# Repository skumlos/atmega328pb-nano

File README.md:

Arduino Mini Pro clone with Atmega328PB

This is basically an Arduino Mini Pro clone but with an Atmega328PB instead of Atmega328P.

Speed 16MHz and 5V.

The reasoning is to have the secondary I2C controller of the PB version, thus PE0 and PE1
pins are pulled to 2.54mm THT holes just like A4/A5 pins of the primary I2C controller.

Remember to burn a bootloader and fuses with a *real* programmer (like another Arduino
turned into an ISP). This requires you to connect to the ICSP pins, MOSI, MISO, SCK,
RESET, 5V and GND. I used a male pin header row  which I didn't solder but just held in
place during programming.

The design is tested and works, but it is hacked together pretty quick so bugs are possible.

(2023) Martin Hejnfelt, martin@hejnfelt.com

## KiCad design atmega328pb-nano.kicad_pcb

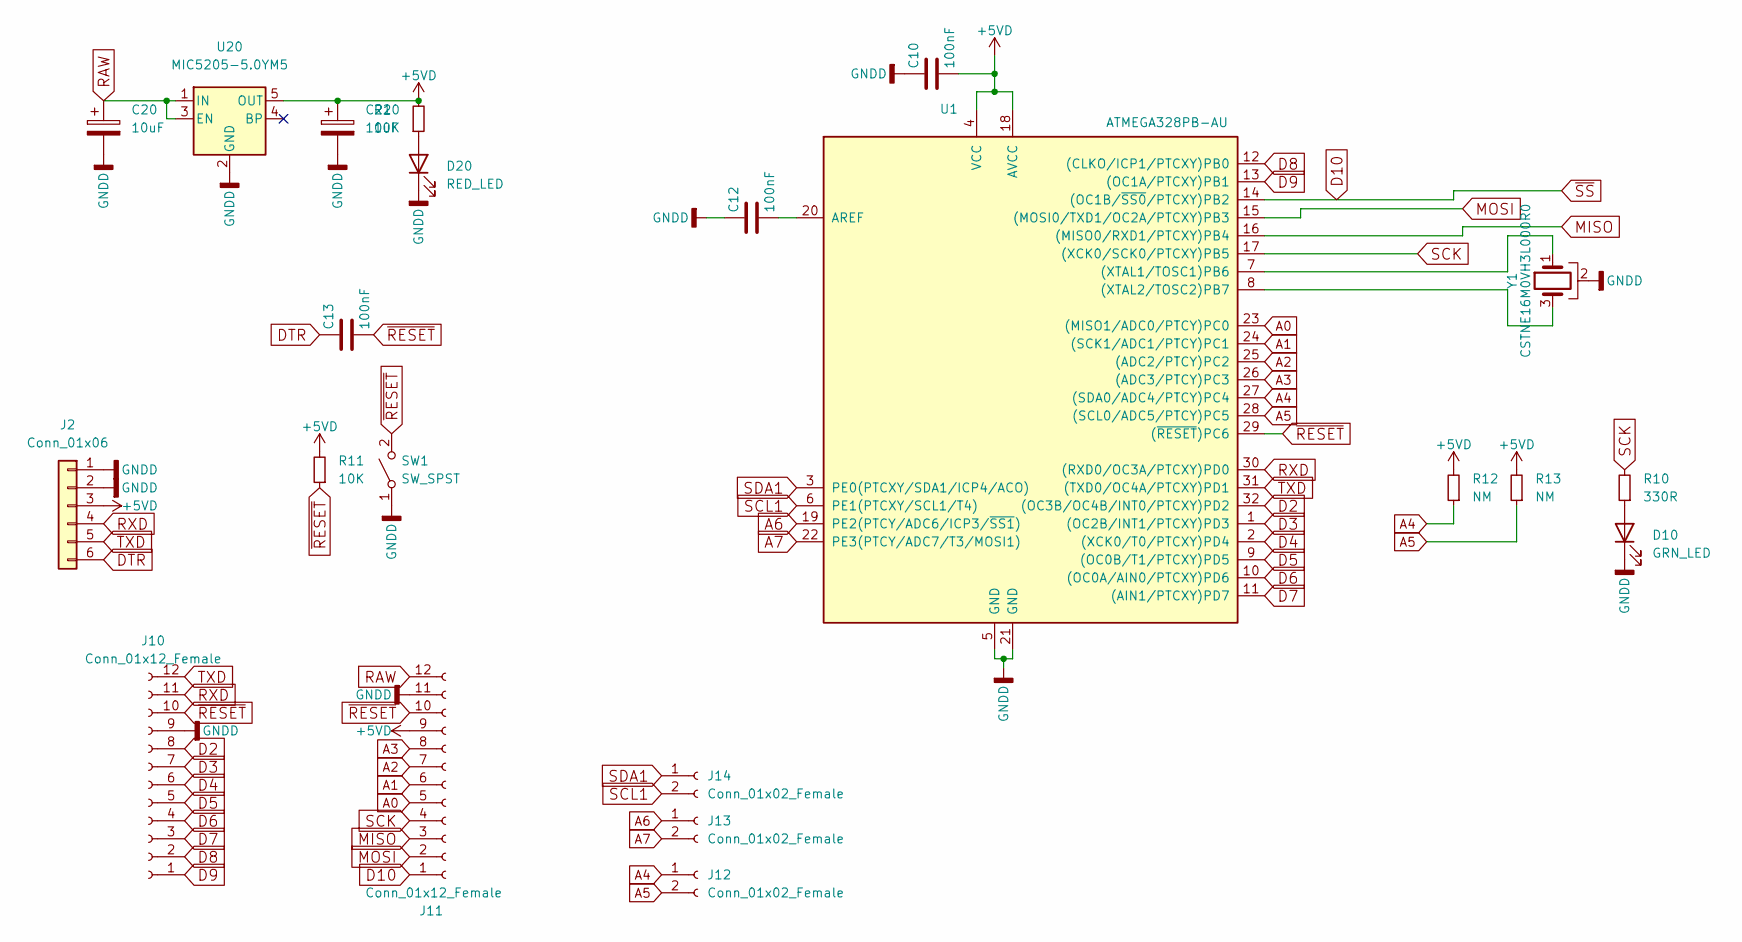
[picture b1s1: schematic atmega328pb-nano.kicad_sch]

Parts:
C10, C12, C13: 100nF; C_0603_1608Metric
C20, C21: 10uF; CP_EIA-3216-18_Kemet-A
D10: GRN_LED; LED_0603_1608Metric
D20: RED_LED; LED_0603_1608Metric
J2: Conn_01x06; PinHeader_1x06_P2.54mm_Horizontal
J10, J11: Conn_01x12_Female; PinHeader_1x12_P2.54mm_Vertical
J12, J13, J14: Conn_01x02_Female; PinHeader_1x02_P2.54mm_Vertical
R10: 330R; R_0603_1608Metric
R11, R20: 10K; R_0603_1608Metric
R12, R13: NM; R_0603_1608Metric
SW1: SW_SPST; SW_Tactile_SPST_NO_Straight_CK_PTS636Sx25SMTRLFS
U1: ATMEGA328PB-AU; TQFP-32_7x7mm_P0.8mm
U20: MIC5205-5.0YM5; SOT-23-5
Y1: CSTNE16M0VH3L000R0; Resonator_SMD_Murata_CSTxExxV-3Pin_3.0x1.1mm

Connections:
+5VD: C10.2, C21.1, J2.3, J11.9, R11.2, R12.2, R13.2, R20.2, U1.4 (VCC), U1.18 (AVCC), U20.5 (OUT)
A0: J11.5, U1.23 ((MISO1/ADC0/PTCY)PC0)
A1: J11.6, U1.24 ((SCK1/ADC1/PTCY)PC1)
A2: J11.7, U1.25 ((ADC2/PTCY)PC2)
A3: J11.8, U1.26 ((ADC3/PTCY)PC3)
A4: J12.1, R12.1, U1.27 ((SDA0/ADC4/PTCY)PC4)
A5: J12.2, R13.1, U1.28 ((SCL0/ADC5/PTCY)PC5)
A6: J13.1, U1.19 (PE2(PTCY/ADC6/ICP3/~SS1))
A7: J13.2, U1.22 (PE3(PTCY/ADC7/T3/MOSI1))
D2: J10.8, U1.32 ((OC3B/OC4B/INT0/PTCXY)PD2)
D3: J10.7, U1.1 ((OC2B/INT1/PTCXY)PD3)
D4: J10.6, U1.2 ((XCK0/T0/PTCXY)PD4)
D5: J10.5, U1.9 ((OC0B/T1/PTCXY)PD5)
D6: J10.4, U1.10 ((OC0A/AIN0/PTCXY)PD6)
D7: J10.3, U1.11 ((AIN1/PTCXY)PD7)
D8: J10.2, U1.12 ((CLKO/ICP1/PTCXY)PB0)
D9: J10.1, U1.13 ((OC1A/PTCXY)PB1)
D10: J11.1, U1.14 ((OC1B/~SS0/PTCXY)PB2)
DTR: C13.1, J2.6
GNDD: C10.1, C12.1, C20.2, C21.2, D10.1 (K), D20.1 (K), J2.1, J2.2, J10.9, J11.11, SW1.1 (A), U1.5 (GND), U1.21 (GND), U20.2 (GND), Y1.2
MISO: J11.3, U1.16 ((MISO0/RXD1/PTCXY)PB4)
MOSI: J11.2, U1.15 ((MOSI0/TXD1/OC2A/PTCXY)PB3)
unnamed: C12.2, U1.20 (AREF)
unnamed: D10.2 (A), R10.1
unnamed: D20.2 (A), R20.1
unnamed: U1.7 ((XTAL1/TOSC1)PB6), Y1.1
unnamed: U1.8 ((XTAL2/TOSC2)PB7), Y1.3
RAW: C20.1, J11.12, U20.1 (IN), U20.3 (EN)
RXD: J2.4, J10.11, U1.30 ((RXD0/OC3A/PTCXY)PD0)
SCK: J11.4, R10.2, U1.17 ((XCK0/SCK0/PTCXY)PB5)
SCL1: J14.2, U1.6 (PE1(PTCXY/SCL1/T4))
SDA1: J14.1, U1.3 (PE0(PTCXY/SDA1/ICP4/ACO))
TXD: J2.5, J10.12, U1.31 ((TXD0/OC4A/PTCXY)PD1)
~RESET: C13.2, J10.10, J11.10, R11.1, SW1.2 (B), U1.29 ((~RESET)PC6)

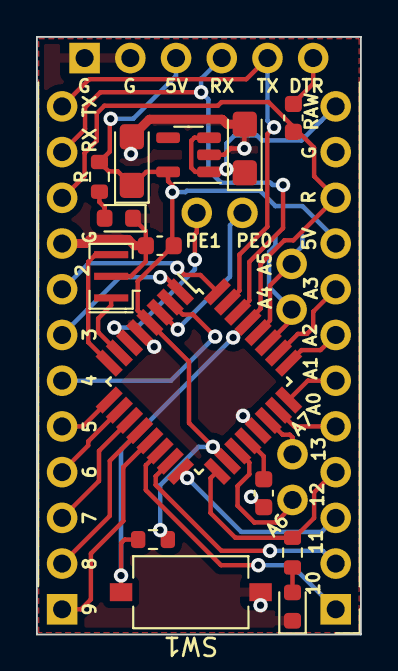
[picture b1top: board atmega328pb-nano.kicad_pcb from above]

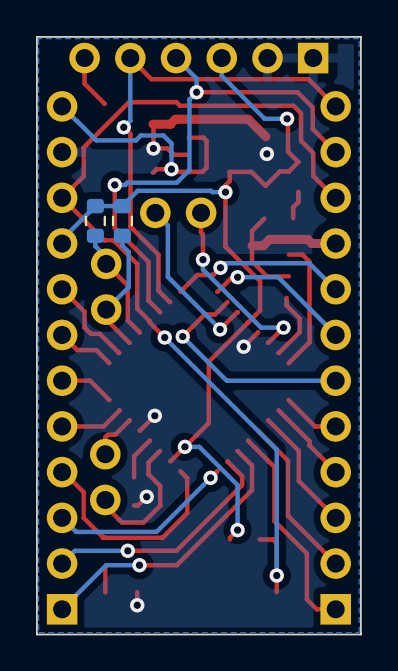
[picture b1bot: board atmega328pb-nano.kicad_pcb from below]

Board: 2 copper layers, 18.0 x 33.2 mm, 22 parts (2 on the bottom side), 34 nets.

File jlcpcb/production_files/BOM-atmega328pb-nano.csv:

Comment,Designator,Footprint,LCSC
330R,R10,R_0603_1608Metric,C105881
ATMEGA328PB-AU,U1,TQFP-32_7x7mm_P0.8mm,C132230
100nF,"C10,C12,C13",C_0603_1608Metric,C14663
RED_LED,D20,LED_0603_1608Metric,C2286
10K,"R11,R20",R_0603_1608Metric,C25804
SW_SPST,SW1,SW_Tactile_SPST_NO_Straight_CK_PTS636Sx25SMTRLFS,C2689642
MIC5205-5.0YM5,U20,SOT-23-5,C70431
10uF,"C20,C21",CP_EIA-3216-18_Kemet-A,C7171
GRN_LED,D10,LED_0603_1608Metric,C72038
CSTNE16M0VH3L000R0,Y1,Resonator_SMD_Murata_CSTxExxV-3Pin_3.0x1.1mm,C882605
Conn_01x12_Female,J11,PinHeader_1x12_P2.54mm_Vertical,
Conn_01x06,J2,PinHeader_1x06_P2.54mm_Horizontal,
Conn_01x12_Female,J10,PinHeader_1x12_P2.54mm_Vertical,
Conn_01x02_Female,J12,PinHeader_1x02_P2.54mm_Vertical,
Conn_01x02_Female,J14,PinHeader_1x02_P2.54mm_Vertical,
Conn_01x02_Female,J13,PinHeader_1x02_P2.54mm_Vertical,
NM,R13,R_0603_1608Metric,
NM,R12,R_0603_1608Metric,

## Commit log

2023-11-11 Added JLCPCB production files
2023-11-12 Add README
